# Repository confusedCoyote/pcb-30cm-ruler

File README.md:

# pcb-30cm-ruler
A Printed Circuit Board ruler with some helpful hints

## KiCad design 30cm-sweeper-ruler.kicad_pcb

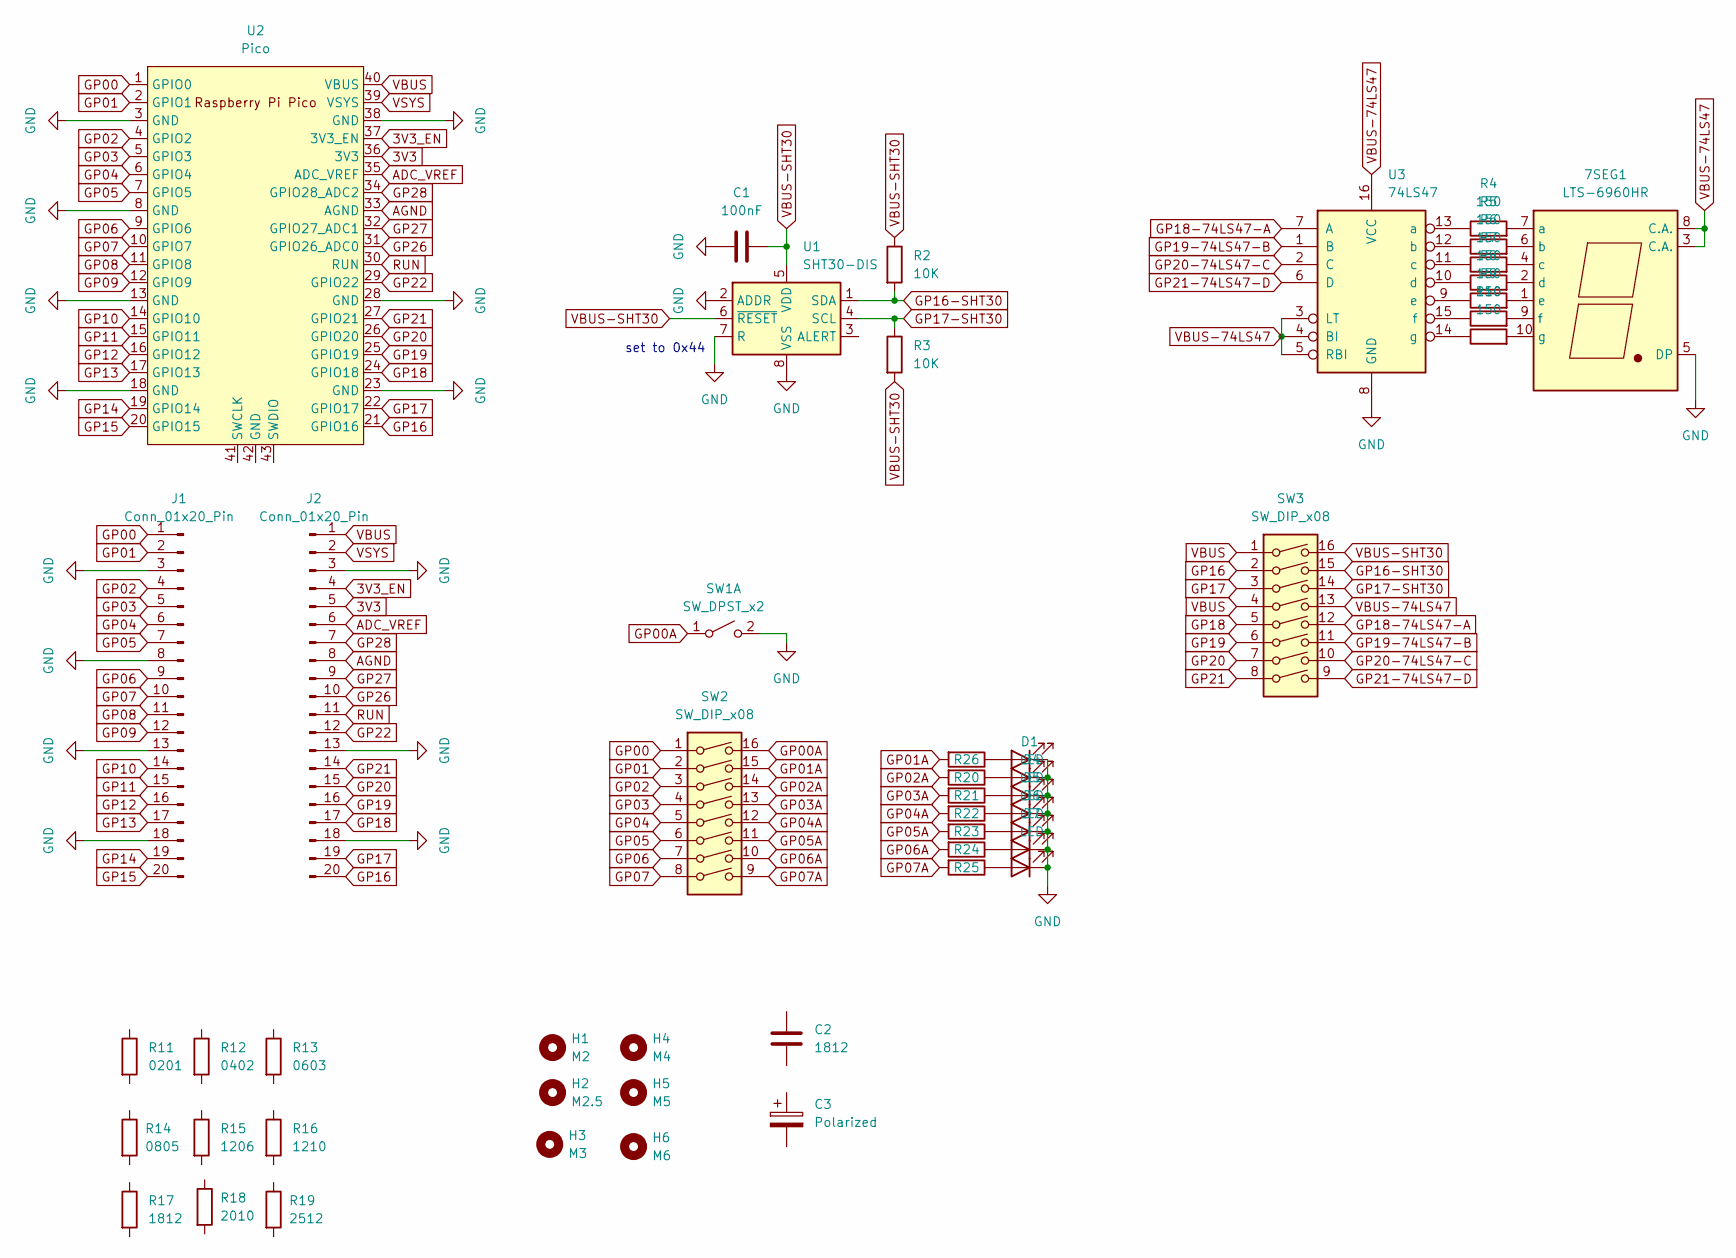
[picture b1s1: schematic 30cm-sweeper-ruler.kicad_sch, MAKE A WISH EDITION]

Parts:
7SEG1: LTS-6960HR; 7SegmentLED_LTS6760_LTS6780
C1: 100nF; C_Disc_D3.4mm_W2.1mm_P2.50mm
C2: 1812; C_1812_4532Metric
C3: Polarized; CP_Elec_3x5.3
D1, D2, D3, D4, D5, D6, D7: LED; LED_D3.0mm
H1: M2; MountingHole_2.2mm_M2
H2: M2.5; MountingHole_2.7mm_M2.5
H3: M3; MountingHole_3.2mm_M3
H4: M4; MountingHole_4.3mm_M4
H5: M5; MountingHole_5.3mm_M5
H6: M6; MountingHole_6.4mm_M6
J1, J2: Conn_01x20_Pin; PinHeader_1x20_P2.54mm_Vertical
R2, R3: 10K; R_0603_1608Metric
R4, R5, R6, R7, R8, R9, R10: 150; R_0603_1608Metric
R11: 0201; R_0201_0603Metric
R12: 0402; R_0402_1005Metric
R13: 0603; R_0603_1608Metric
R14: 0805; R_0805_2012Metric
R15: 1206; R_1206_3216Metric
R16: 1210; R_1210_3225Metric
R17: 1812; R_1812_4532Metric
R18: 2010; R_2010_5025Metric
R19: 2512; R_2512_6332Metric
R20, R21, R22, R23, R24, R25, R26: R_Axial_DIN0207_L6.3mm_D2.5mm_P10.16mm_Horizontal
SW1: SW_DPST_x2; SW_PUSH-12mm
SW2, SW3: SW_DIP_x08; SW_DIP_SPSTx08_Slide_6.7x21.88mm_W7.62mm_P2.54mm_LowProfile
U1: SHT30-DIS; Sensirion_DFN-8-1EP_2.5x2.5mm_P0.5mm_EP1.1x1.7mm
U2: Pico; RPi_Pico_SMD_TH
U3: 74LS47; SOIC127P600X175-16N

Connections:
3V3: J2.5, U2.36 (3V3)
3V3_EN: J2.4, U2.37 (3V3_EN)
ADC_VREF: J2.6, U2.35 (ADC_VREF)
AGND: J2.8, U2.33 (AGND)
GND: 7SEG1.5 (DP), C1.1, D1.1 (K), D2.1 (K), D3.1 (K), D4.1 (K), D5.1 (K), D6.1 (K), D7.1 (K), J1.3, J1.8, J1.13, J1.18, J2.3, J2.13, J2.18, SW1.2 (B), U1.2 (ADDR), U1.7 (R), U1.8 (VSS), U1.9 (VSS), U2.3 (GND), U2.8 (GND), U2.13 (GND), U2.18 (GND), U2.23 (GND), U2.28 (GND), U2.38 (GND), U3.8 (GND)
GP00: J1.1, SW2.1, U2.1 (GPIO0)
GP00A: SW1.1 (A), SW2.16
GP01: J1.2, SW2.2, U2.2 (GPIO1)
GP01A: R26.2, SW2.15
GP02: J1.4, SW2.3, U2.4 (GPIO2)
GP02A: R20.2, SW2.14
GP03: J1.5, SW2.4, U2.5 (GPIO3)
GP03A: R21.2, SW2.13
GP04: J1.6, SW2.5, U2.6 (GPIO4)
GP04A: R22.2, SW2.12
GP05: J1.7, SW2.6, U2.7 (GPIO5)
GP05A: R23.2, SW2.11
GP06: J1.9, SW2.7, U2.9 (GPIO6)
GP06A: R24.2, SW2.10
GP07: J1.10, SW2.8, U2.10 (GPIO7)
GP07A: R25.2, SW2.9
GP08: J1.11, U2.11 (GPIO8)
GP09: J1.12, U2.12 (GPIO9)
GP10: J1.14, U2.14 (GPIO10)
GP11: J1.15, U2.15 (GPIO11)
GP12: J1.16, U2.16 (GPIO12)
GP13: J1.17, U2.17 (GPIO13)
GP14: J1.19, U2.19 (GPIO14)
GP15: J1.20, U2.20 (GPIO15)
GP16: J2.20, SW3.2, U2.21 (GPIO16)
GP16-SHT30: R2.2, SW3.15, U1.1 (SDA)
GP17: J2.19, SW3.3, U2.22 (GPIO17)
GP17-SHT30: R3.1, SW3.14, U1.4 (SCL)
GP18: J2.17, SW3.5, U2.24 (GPIO18)
GP18-74LS47-A: SW3.12, U3.7 (A)
GP19: J2.16, SW3.6, U2.25 (GPIO19)
GP19-74LS47-B: SW3.11, U3.1 (B)
GP20: J2.15, SW3.7, U2.26 (GPIO20)
GP20-74LS47-C: SW3.10, U3.2 (C)
GP21: J2.14, SW3.8, U2.27 (GPIO21)
GP21-74LS47-D: SW3.9, U3.6 (D)
GP22: J2.12, U2.29 (GPIO22)
GP26: J2.10, U2.31 (GPIO26_ADC0)
GP27: J2.9, U2.32 (GPIO27_ADC1)
GP28: J2.7, U2.34 (GPIO28_ADC2)
unnamed: 7SEG1.7 (a), R4.2
unnamed: 7SEG1.6 (b), R5.2
unnamed: 7SEG1.4 (c), R6.2
unnamed: 7SEG1.2 (d), R7.2
unnamed: 7SEG1.1 (e), R8.2
unnamed: 7SEG1.9 (f), R9.2
unnamed: 7SEG1.10 (g), R10.2
unnamed: D1.2 (A), R26.1
unnamed: D2.2 (A), R20.1
unnamed: D3.2 (A), R21.1
unnamed: D4.2 (A), R22.1
unnamed: D5.2 (A), R23.1
unnamed: D6.2 (A), R24.1
unnamed: D7.2 (A), R25.1
unnamed: R4.1, U3.13 (a)
unnamed: R5.1, U3.12 (b)
unnamed: R6.1, U3.11 (c)
unnamed: R7.1, U3.10 (d)
unnamed: R8.1, U3.9 (e)
unnamed: R9.1, U3.15 (f)
unnamed: R10.1, U3.14 (g)
RUN: J2.11, U2.30 (RUN)
VBUS: J2.1, SW3.1, SW3.4, U2.40 (VBUS)
VBUS-74LS47: 7SEG1.3 (C.A.), 7SEG1.8 (C.A.), SW3.13, U3.3 (LT), U3.4 (BI), U3.5 (RBI), U3.16 (VCC)
VBUS-SHT30: C1.2, R2.1, R3.2, SW3.16, U1.5 (VDD), U1.6 (~RESET)
VSYS: J2.2, U2.39 (VSYS)

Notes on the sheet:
set to 0x44

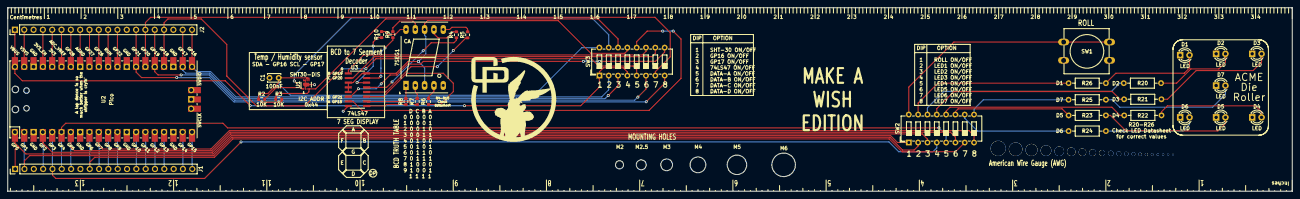
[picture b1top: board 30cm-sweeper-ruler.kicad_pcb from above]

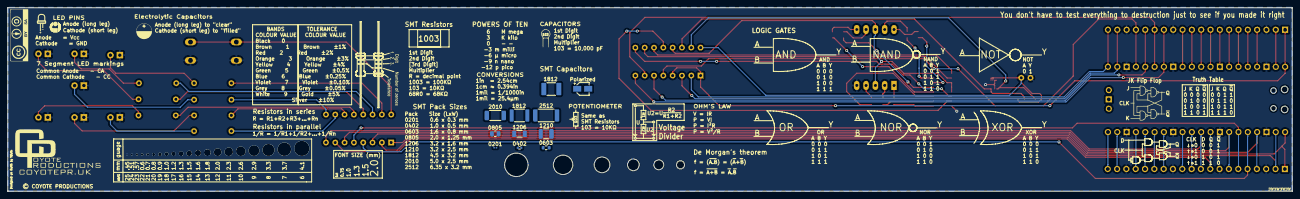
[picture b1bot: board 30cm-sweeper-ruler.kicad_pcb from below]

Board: 2 copper layers, 350.0 x 50.0 mm, 50 parts (11 on the bottom side), 71 nets.

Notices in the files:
30cm-sweeper-ruler.kicad_pcb:
© COYOTE PRODUCTIONS
